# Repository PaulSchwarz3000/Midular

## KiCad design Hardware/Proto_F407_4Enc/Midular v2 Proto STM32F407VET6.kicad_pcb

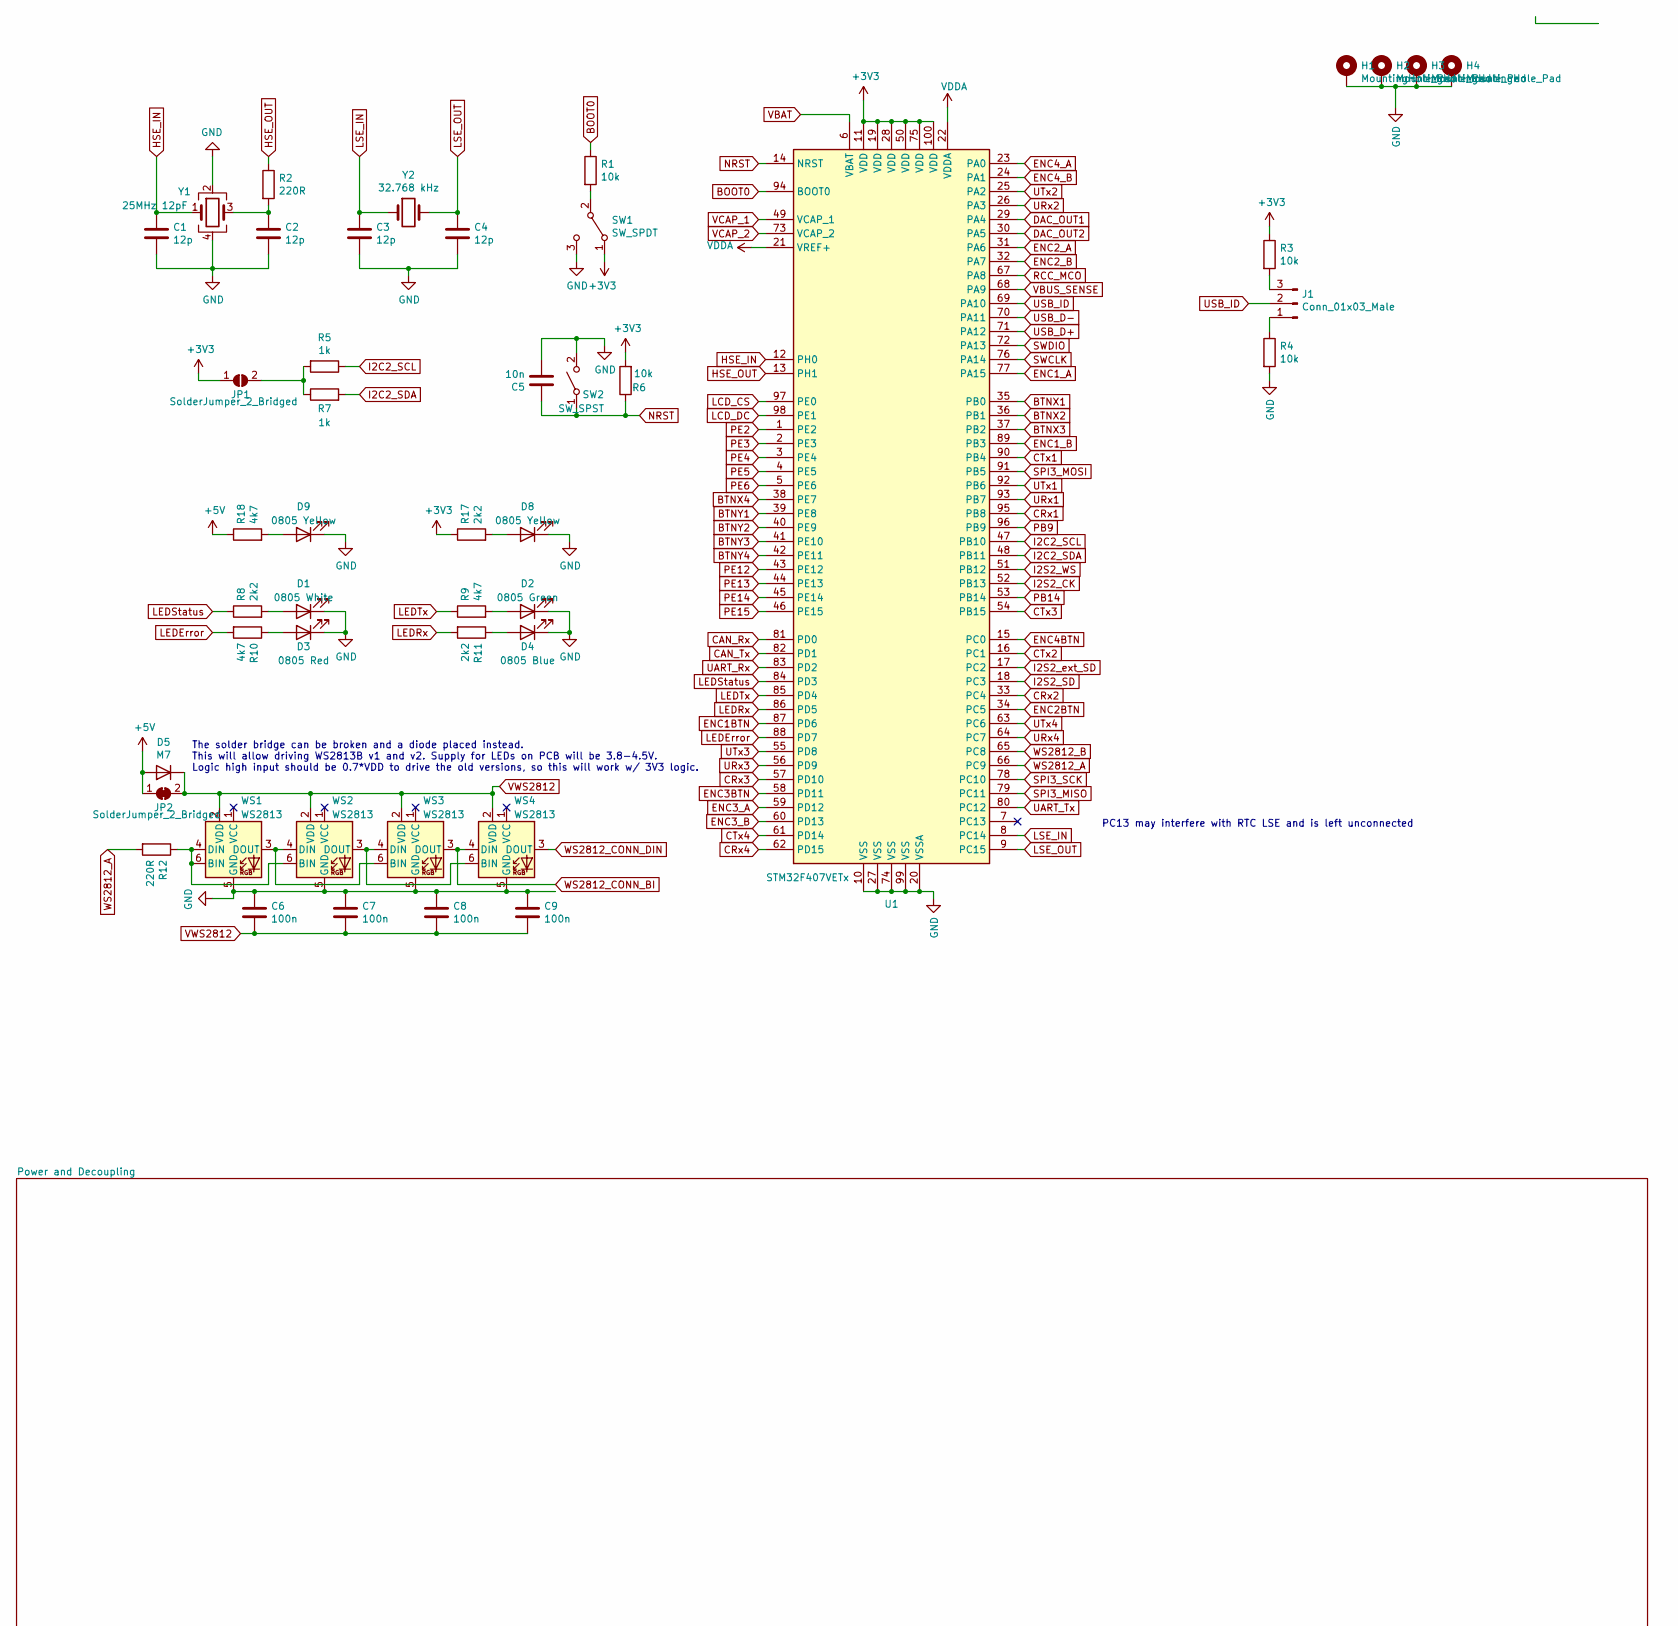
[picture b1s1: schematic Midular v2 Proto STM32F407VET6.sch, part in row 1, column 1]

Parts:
C1, C2, C3, C4: 12p; C_0603_1608Metric_Pad1.08x0.95mm_HandSolder; LCSC C38523
C5: 10n; C_0402_1005Metric_Pad0.74x0.62mm_HandSolder; LCSC C15195
C6, C7, C8, C9: 100n; C_0402_1005Metric; LCSC C1525
D1: 0805 White; LED_0805_2012Metric_Castellated; LCSC C34499
D2: 0805 Green; LED_0805_2012Metric_Castellated; LCSC C2297
D3: 0805 Red; LED_0805_2012Metric_Castellated; LCSC C84256
D4: 0805 Blue; LED_0805_2012Metric_Castellated; LCSC C2293
D5: M7; D_SMA; LCSC C95872
D8, D9: 0805 Yellow; LED_0805_2012Metric_Castellated; LCSC C2296
H1, H2, H3, H4: MountingHole_Pad; MountingHole_3.2mm_M3_ISO7380_Pad
J1: Conn_01x03_Male; PinHeader_1x03_P2.54mm_Vertical
JP1: SolderJumper_2_Bridged; SolderJumper-2_P1.3mm_Open_RoundedPad1.0x1.5mm
JP2: SolderJumper_2_Bridged; SolderJumper-2_P1.3mm_Bridged_RoundedPad1.0x1.5mm
R1, R3, R4, R6: 10k; R_0402_1005Metric; LCSC C25744
R2, R12: 220R; R_0805_2012Metric; LCSC C17557
R5, R7: 1k; R_1206_3216Metric_Pad1.30x1.75mm_HandSolder; LCSC C4410
R8, R11, R17: 2k2; R_0805_2012Metric_Pad1.20x1.40mm_HandSolder; LCSC C17520
R9, R10, R18: 4k7; R_0805_2012Metric_Pad1.20x1.40mm_HandSolder; LCSC C17673
SW1: SW_SPDT; SK3296S01L3; LCSC C319019
SW2: SW_SPST; K21107STA4SW06; LCSC C11814
U1: STM32F407VETx; LQFP-100_14x14mm_P0.5mm; LCSC C28730
WS1, WS2, WS3, WS4: WS2813; LED_WS2812_PLCC6_5.0x5.0mm_P1.6mm
Y1: 25MHz 12pF; Crystal_SMD_3225-4Pin_3.2x2.5mm; Part Nr X322525MOB4SI; LCSC C9006
Y2: 32.768 kHz; Crystal_SMD_3215-2Pin_3.2x1.5mm; LCSC C32346

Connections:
+3V3: JP1.1 (A), R3.1, R6.2, R17.1, SW1.1 (A), U1.11 (VDD), U1.19 (VDD), U1.28 (VDD), U1.50 (VDD), U1.75 (VDD), U1.100 (VDD); also elsewhere on the board
+5V: D5.2 (A), JP2.1 (A), R18.1; also elsewhere on the board
BOOT0: R1.1, U1.94 (BOOT0)
BTNX1: U1.35 (PB0); also elsewhere on the board
BTNX2: U1.36 (PB1); also elsewhere on the board
BTNX3: U1.37 (PB2); also elsewhere on the board
BTNX4: U1.38 (PE7); also elsewhere on the board
BTNY1: U1.39 (PE8); also elsewhere on the board
BTNY2: U1.40 (PE9); also elsewhere on the board
BTNY3: U1.41 (PE10); also elsewhere on the board
BTNY4: U1.42 (PE11); also elsewhere on the board
CAN_Rx: U1.81 (PD0); also elsewhere on the board
CAN_Tx: U1.82 (PD1); also elsewhere on the board
CRx1: U1.95 (PB8); also elsewhere on the board
CRx2: U1.33 (PC4); also elsewhere on the board
CRx3: U1.57 (PD10); also elsewhere on the board
CRx4: U1.62 (PD15); also elsewhere on the board
CTx1: U1.90 (PB4); also elsewhere on the board
CTx2: U1.16 (PC1); also elsewhere on the board
CTx3: U1.54 (PB15); also elsewhere on the board
CTx4: U1.61 (PD14); also elsewhere on the board
DAC_OUT1: U1.29 (PA4); also elsewhere on the board
DAC_OUT2: U1.30 (PA5); also elsewhere on the board
ENC1BTN: U1.87 (PD6); also elsewhere on the board
ENC1_A: U1.77 (PA15); also elsewhere on the board
ENC1_B: U1.89 (PB3); also elsewhere on the board
ENC2BTN: U1.34 (PC5); also elsewhere on the board
ENC2_A: U1.31 (PA6); also elsewhere on the board
ENC2_B: U1.32 (PA7); also elsewhere on the board
ENC3BTN: U1.58 (PD11); also elsewhere on the board
ENC3_A: U1.59 (PD12); also elsewhere on the board
ENC3_B: U1.60 (PD13); also elsewhere on the board
ENC4BTN: U1.15 (PC0); also elsewhere on the board
ENC4_A: U1.23 (PA0); also elsewhere on the board
ENC4_B: U1.24 (PA1); also elsewhere on the board
GND: C1.2, C2.2, C3.2, C4.2, C5.2, C6.1, C7.1, C8.1, C9.1, D1.1 (K), D2.1 (K), D3.1 (K), D4.1 (K), D8.1 (K), D9.1 (K), H1.1, H2.1, H3.1, H4.1, R4.2, SW1.3 (C), SW2.2 (B), U1.10 (VSS), U1.20 (VSSA), U1.27 (VSS), U1.74 (VSS), U1.99 (VSS), WS1.5 (GND), WS2.5 (GND), WS3.5 (GND), WS4.5 (GND), Y1.2, Y1.4; also elsewhere on the board
HSE_IN: C1.1, U1.12 (PH0), Y1.1
HSE_OUT: R2.1, U1.13 (PH1)
I2C2_SCL: R5.1, U1.47 (PB10); also elsewhere on the board
I2C2_SDA: R7.2, U1.48 (PB11); also elsewhere on the board
I2S2_CK: U1.52 (PB13); also elsewhere on the board
I2S2_SD: U1.18 (PC3); also elsewhere on the board
I2S2_WS: U1.51 (PB12); also elsewhere on the board
I2S2_ext_SD: U1.17 (PC2); also elsewhere on the board
LCD_CS: U1.97 (PE0); also elsewhere on the board
LCD_DC: U1.98 (PE1); also elsewhere on the board
LEDError: R10.2, U1.88 (PD7)
LEDRx: R11.2, U1.86 (PD5)
LEDStatus: R8.1, U1.84 (PD3)
LEDTx: R9.1, U1.85 (PD4)
LSE_IN: C3.1, U1.8 (PC14), Y2.1
LSE_OUT: C4.1, U1.9 (PC15), Y2.2
NRST: C5.1, R6.1, SW2.1 (A), U1.14 (NRST); also elsewhere on the board
unnamed: C2.1, R2.2, Y1.3
unnamed: D1.2 (A), R8.2
unnamed: D2.2 (A), R9.2
unnamed: D3.2 (A), R10.1
unnamed: D4.2 (A), R11.1
unnamed: D8.2 (A), R17.2
unnamed: D9.2 (A), R18.2
unnamed: J1.1, R4.1
unnamed: J1.3, R3.2
unnamed: JP1.2 (B), R5.2, R7.1
unnamed: R1.2, SW1.2 (B)
unnamed: R12.1, WS1.4 (DIN), WS1.6 (BIN), WS2.6 (BIN)
unnamed: WS1.3 (DOUT), WS2.4 (DIN), WS3.6 (BIN)
unnamed: WS2.3 (DOUT), WS3.4 (DIN), WS4.6 (BIN)
PB9: U1.96 (PB9); also elsewhere on the board
PB14: U1.53 (PB14); also elsewhere on the board
PE2: U1.1 (PE2); also elsewhere on the board
PE3: U1.2 (PE3); also elsewhere on the board
PE4: U1.3 (PE4); also elsewhere on the board
PE5: U1.4 (PE5); also elsewhere on the board
PE6: U1.5 (PE6); also elsewhere on the board
PE12: U1.43 (PE12); also elsewhere on the board
PE13: U1.44 (PE13); also elsewhere on the board
PE14: U1.45 (PE14); also elsewhere on the board
PE15: U1.46 (PE15); also elsewhere on the board
RCC_MCO: U1.67 (PA8); also elsewhere on the board
SPI3_MISO: U1.79 (PC11); also elsewhere on the board
SPI3_MOSI: U1.91 (PB5); also elsewhere on the board
SPI3_SCK: U1.78 (PC10); also elsewhere on the board
SWCLK: U1.76 (PA14); also elsewhere on the board
SWDIO: U1.72 (PA13); also elsewhere on the board
UART_Rx: U1.83 (PD2); also elsewhere on the board
UART_Tx: U1.80 (PC12); also elsewhere on the board
URx1: U1.93 (PB7); also elsewhere on the board
URx2: U1.26 (PA3); also elsewhere on the board
URx3: U1.56 (PD9); also elsewhere on the board
URx4: U1.64 (PC7); also elsewhere on the board
USB_D+: U1.71 (PA12); also elsewhere on the board
USB_D-: U1.70 (PA11); also elsewhere on the board
USB_ID: J1.2, U1.69 (PA10)
UTx1: U1.92 (PB6); also elsewhere on the board
UTx2: U1.25 (PA2); also elsewhere on the board
UTx3: U1.55 (PD8); also elsewhere on the board
UTx4: U1.63 (PC6); also elsewhere on the board
VBAT: U1.6 (VBAT); also elsewhere on the board
VBUS_SENSE: U1.68 (PA9); also elsewhere on the board
VCAP_1: U1.49 (VCAP_1); also elsewhere on the board
VCAP_2: U1.73 (VCAP_2); also elsewhere on the board
VDDA: U1.21 (VREF+), U1.22 (VDDA); also elsewhere on the board
VWS2812: C6.2, C7.2, C8.2, C9.2, D5.1 (K), JP2.2 (B), WS1.2 (VDD), WS2.2 (VDD), WS3.2 (VDD), WS4.2 (VDD)
WS2812_A: R12.2, U1.66 (PC9)
WS2812_B: U1.65 (PC8); also elsewhere on the board
WS2812_CONN_BI: WS3.3 (DOUT), WS4.4 (DIN); also elsewhere on the board
WS2812_CONN_DIN: WS4.3 (DOUT); also elsewhere on the board

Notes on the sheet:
The solder bridge can be broken and a diode placed instead. This will allow driving WS2813B v1 and v2. Supply for LEDs on PCB will be 3.8-4.5V. Logic high input should be 0.7*VDD to drive the old versions, so this will work w/ 3V3 logic.
PC13 may interfere with RTC LSE and is left unconnected

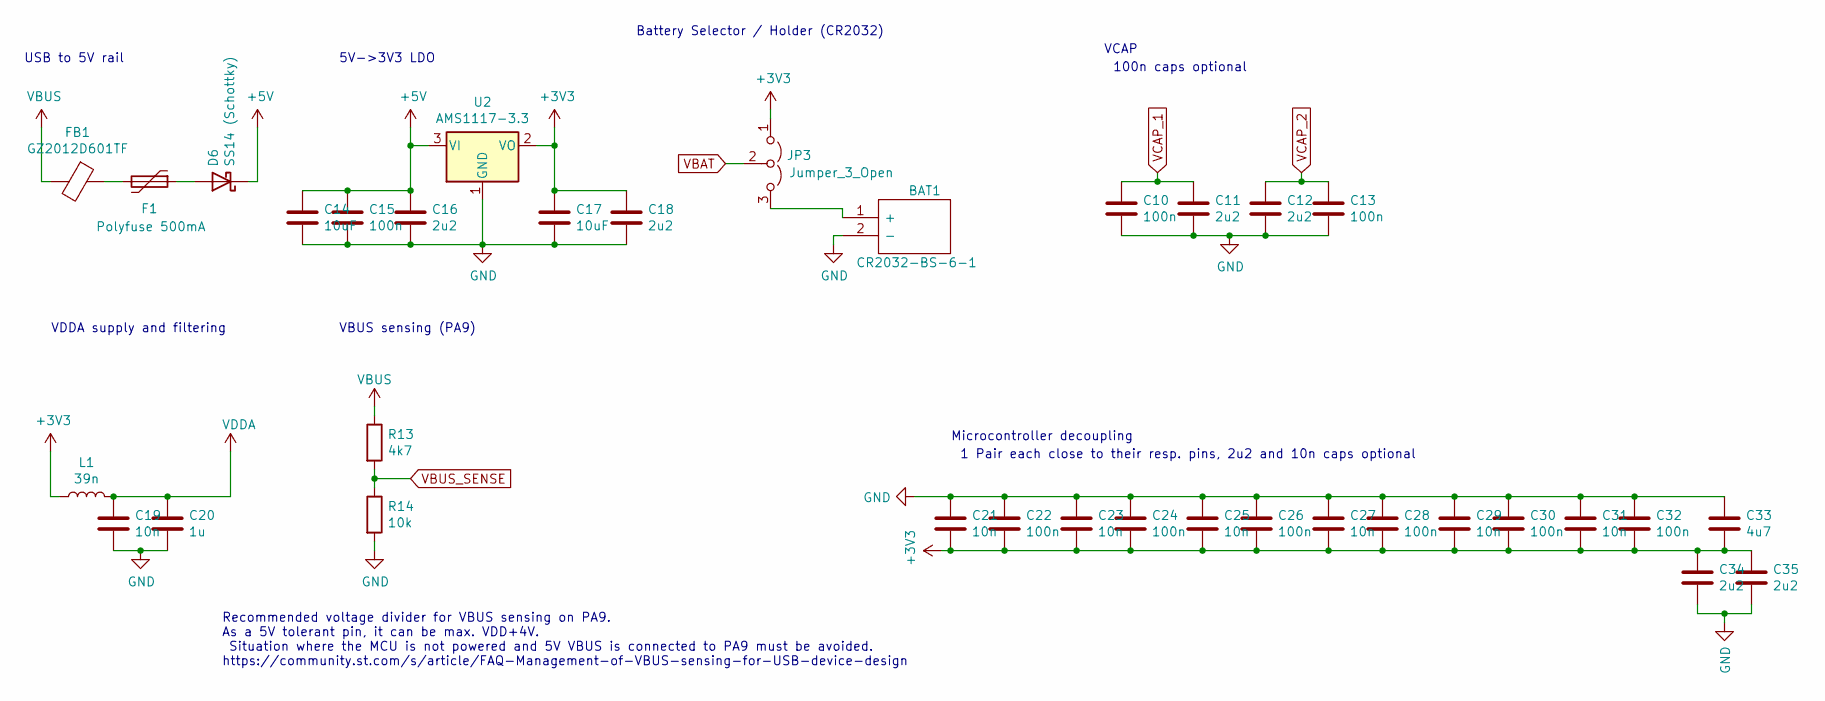
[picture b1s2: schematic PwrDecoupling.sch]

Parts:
BAT1: CR2032-BS-6-1; CR2032BS61; Manufacturer_Part_Number CR2032-BS-6-1
C10, C13, C15, C22, C24, C26, C28, C30, C32: 100n; C_0402_1005Metric; LCSC C1525
C11, C12, C16, C18, C34, C35: 2u2; C_0402_1005Metric; LCSC C12530
C14, C17: 10uF; C_0805_2012Metric_Pad1.18x1.45mm_HandSolder; LCSC C15850
C19, C21, C23, C25, C27, C29, C31: 10n; C_0402_1005Metric; LCSC C15195
C20: 1u; C_0402_1005Metric; LCSC C52923
C33: 4u7; C_0402_1005Metric; LCSC C19666
D6: SS14 (Schottky); D_SMA-SMB_Universal_Handsoldering; LCSC C2480
F1: Polyfuse 500mA; Fuse_1206_3216Metric_Castellated; LCSC C69688
FB1: GZ2012D601TF; L_0805_2012Metric; LCSC C1017
JP3: Jumper_3_Open; PinHeader_1x03_P2.54mm_Vertical
L1: 39n; L_0402_1005Metric; LCSC C26443
R13: 4k7; R_0402_1005Metric; LCSC C25900
R14: 10k; R_0402_1005Metric; LCSC C25744
U2: AMS1117-3.3; SOT-223-3_TabPin2; LCSC C6186

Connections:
+3V3: C17.1, C18.1, C21.2, C22.2, C23.2, C24.2, C25.2, C26.2, C27.2, C28.2, C29.2, C30.2, C31.2, C32.2, C33.2, C34.1, C35.1, JP3.1 (A), L1.1, U2.2 (VO); also elsewhere on the board
+5V: C14.1, C15.1, C16.1, D6.1 (K), U2.3 (VI); also elsewhere on the board
GND: BAT1.2 (-), C10.2, C11.2, C12.2, C13.2, C14.2, C15.2, C16.2, C17.2, C18.2, C19.2, C20.2, C21.1, C22.1, C23.1, C24.1, C25.1, C26.1, C27.1, C28.1, C29.1, C30.1, C31.1, C32.1, C33.1, C34.2, C35.2, R14.2, U2.1 (GND); also elsewhere on the board
unnamed: BAT1.1 (+), JP3.3 (B)
unnamed: D6.2 (A), F1.1
unnamed: F1.2, FB1.1
VBAT: JP3.2 (C); also elsewhere on the board
VBUS: FB1.2, R13.1; also elsewhere on the board
VBUS_SENSE: R13.2, R14.1; also elsewhere on the board
VCAP_1: C10.1, C11.1; also elsewhere on the board
VCAP_2: C12.1, C13.1; also elsewhere on the board
VDDA: C19.1, C20.1, L1.2; also elsewhere on the board

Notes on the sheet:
USB to 5V rail
Battery Selector / Holder (CR2032)
Microcontroller decoupling
1 Pair each close to their resp. pins, 2u2 and 10n caps optional
VCAP
100n caps optional
VDDA supply and filtering
VBUS sensing (PA9)
Recommended voltage divider for VBUS sensing on PA9. As a 5V tolerant pin, it can be max. VDD+4V. Situation where the MCU is not powered and 5V VBUS is connected to PA9 must be avoided. https://community.st.com/s/article/FAQ-Management-of-VBUS-sensing-for-USB-device-design
5V->3V3 LDO

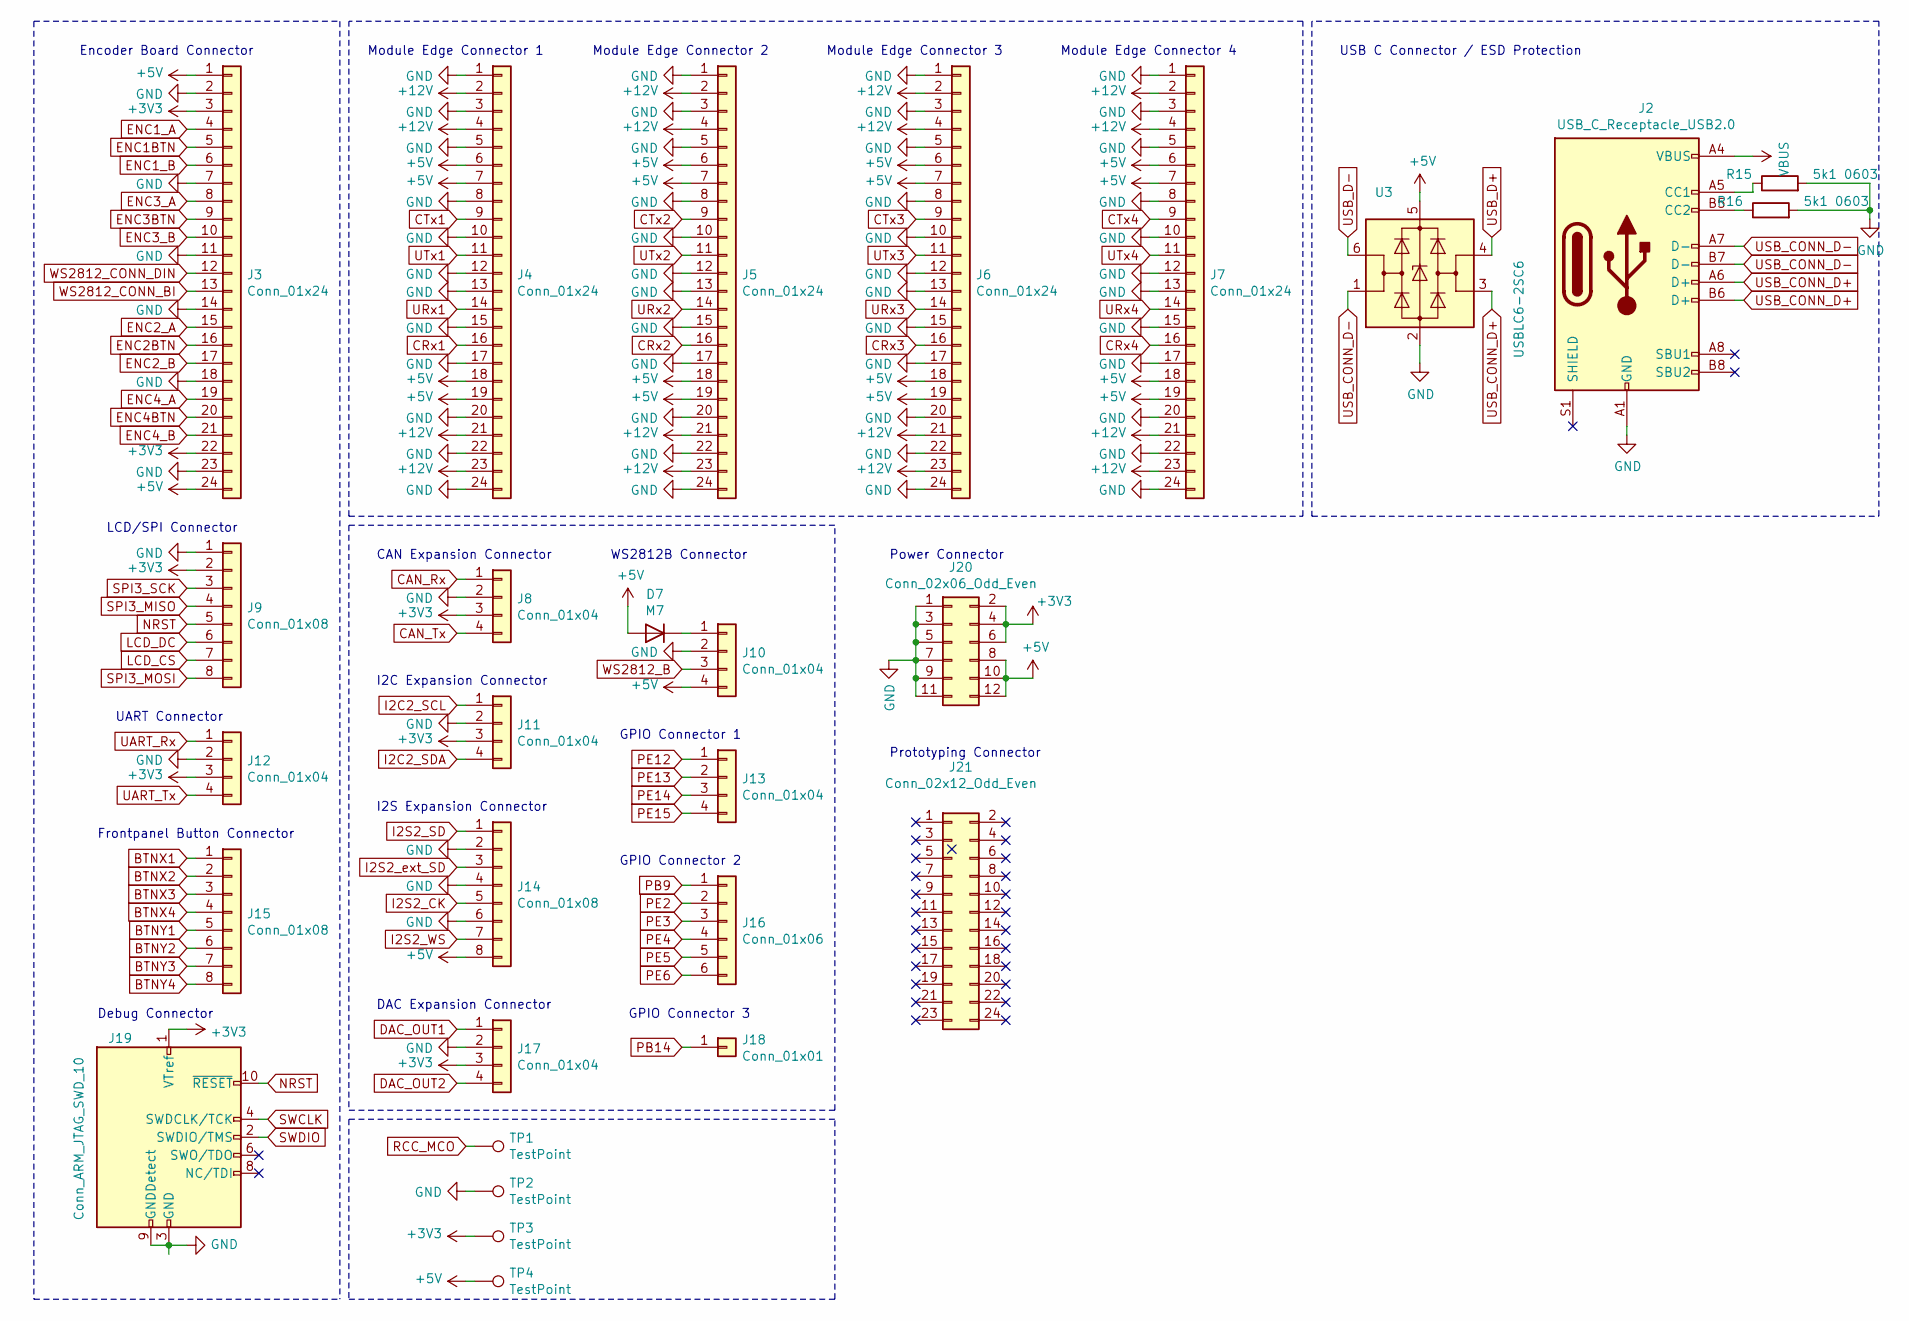
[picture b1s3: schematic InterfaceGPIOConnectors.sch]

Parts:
D7: M7; D_SMA; LCSC C95872
J2: USB_C_Receptacle_USB2.0; TYPEC304SACP16; LCSC C720630
J3: Conn_01x24; FPC_24_AFC24-S24FIC-00
J4, J5, J6, J7: Conn_01x24; FPC_24_AFC24-S24FIC-00; LCSC C262292
J8, J10, J11, J12, J13, J17: Conn_01x04; PinHeader_1x04_P2.54mm_Vertical
J9, J14, J15: Conn_01x08; PinHeader_1x08_P2.54mm_Vertical
J16: Conn_01x06; PinHeader_1x06_P2.54mm_Vertical
J18: Conn_01x01; PinHeader_1x01_P2.54mm_Vertical
J19: Conn_ARM_JTAG_SWD_10; PinHeader_2x05_P1.27mm_Vertical_SMD
J20: Conn_02x06_Odd_Even; PinHeader_2x06_P2.54mm_Vertical
J21: Conn_02x12_Odd_Even; PinHeader_2x12_P2.54mm_Vertical
R15, R16: 5k1 0603; R_0603_1608Metric_Pad0.98x0.95mm_HandSolder; LCSC C23186
TP1, TP2, TP3, TP4: TestPoint; TestPoint_Pad_D2.0mm
U3: USBLC6-2SC6; SOT-23-6; LCSC C7519

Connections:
+3V3: J3.3, J3.22, J8.3, J9.2, J11.3, J12.3, J17.3, J19.1 (VTref), J20.2, J20.4, J20.6, TP3.1; also elsewhere on the board
+5V: D7.2 (A), J3.1, J3.24, J4.6, J4.7, J4.18, J4.19, J5.6, J5.7, J5.18, J5.19, J6.6, J6.7, J6.18, J6.19, J7.6, J7.7, J7.18, J7.19, J10.4, J14.8, J20.8, J20.10, J20.12, TP4.1, U3.5 (VBUS); also elsewhere on the board
+12V: J4.2, J4.4, J4.21, J4.23, J5.2, J5.4, J5.21, J5.23, J6.2, J6.4, J6.21, J6.23, J7.2, J7.4, J7.21, J7.23
BTNX1: J15.1; also elsewhere on the board
BTNX2: J15.2; also elsewhere on the board
BTNX3: J15.3; also elsewhere on the board
BTNX4: J15.4; also elsewhere on the board
BTNY1: J15.5; also elsewhere on the board
BTNY2: J15.6; also elsewhere on the board
BTNY3: J15.7; also elsewhere on the board
BTNY4: J15.8; also elsewhere on the board
CAN_Rx: J8.1; also elsewhere on the board
CAN_Tx: J8.4; also elsewhere on the board
CRx1: J4.16; also elsewhere on the board
CRx2: J5.16; also elsewhere on the board
CRx3: J6.16; also elsewhere on the board
CRx4: J7.16; also elsewhere on the board
CTx1: J4.9; also elsewhere on the board
CTx2: J5.9; also elsewhere on the board
CTx3: J6.9; also elsewhere on the board
CTx4: J7.9; also elsewhere on the board
DAC_OUT1: J17.1; also elsewhere on the board
DAC_OUT2: J17.4; also elsewhere on the board
ENC1BTN: J3.5; also elsewhere on the board
ENC1_A: J3.4; also elsewhere on the board
ENC1_B: J3.6; also elsewhere on the board
ENC2BTN: J3.16; also elsewhere on the board
ENC2_A: J3.15; also elsewhere on the board
ENC2_B: J3.17; also elsewhere on the board
ENC3BTN: J3.9; also elsewhere on the board
ENC3_A: J3.8; also elsewhere on the board
ENC3_B: J3.10; also elsewhere on the board
ENC4BTN: J3.20; also elsewhere on the board
ENC4_A: J3.19; also elsewhere on the board
ENC4_B: J3.21; also elsewhere on the board
GND: J2.A1 (GND), J2.A12 (GND), J2.B1 (GND), J2.B12 (GND), J3.2, J3.7, J3.11, J3.14, J3.18, J3.23, J4.1, J4.3, J4.5, J4.8, J4.10, J4.12, J4.13, J4.15, J4.17, J4.20, J4.22, J4.24, J5.1, J5.3, J5.5, J5.8, J5.10, J5.12, J5.13, J5.15, J5.17, J5.20, J5.22, J5.24, J6.1, J6.3, J6.5, J6.8, J6.10, J6.12, J6.13, J6.15, J6.17, J6.20, J6.22, J6.24, J7.1, J7.3, J7.5, J7.8, J7.10, J7.12, J7.13, J7.15, J7.17, J7.20, J7.22, J7.24, J8.2, J9.1, J10.2, J11.2, J12.2, J14.2, J14.4, J14.6, J17.2, J19.3 (GND), J19.5 (GND), J19.9 (GNDDetect), J20.1, J20.3, J20.5, J20.7, J20.9, J20.11, R15.2, R16.2, TP2.1, U3.2 (GND); also elsewhere on the board
I2C2_SCL: J11.1; also elsewhere on the board
I2C2_SDA: J11.4; also elsewhere on the board
I2S2_CK: J14.5; also elsewhere on the board
I2S2_SD: J14.1; also elsewhere on the board
I2S2_WS: J14.7; also elsewhere on the board
I2S2_ext_SD: J14.3; also elsewhere on the board
LCD_CS: J9.7; also elsewhere on the board
LCD_DC: J9.6; also elsewhere on the board
NRST: J9.5, J19.10 (~RESET~); also elsewhere on the board
unnamed: D7.1 (K), J10.1
unnamed: J2.A5 (CC1), R15.1
unnamed: J2.B5 (CC2), R16.1
PB9: J16.1; also elsewhere on the board
PB14: J18.1; also elsewhere on the board
PE2: J16.2; also elsewhere on the board
PE3: J16.3; also elsewhere on the board
PE4: J16.4; also elsewhere on the board
PE5: J16.5; also elsewhere on the board
PE6: J16.6; also elsewhere on the board
PE12: J13.1; also elsewhere on the board
PE13: J13.2; also elsewhere on the board
PE14: J13.3; also elsewhere on the board
PE15: J13.4; also elsewhere on the board
RCC_MCO: TP1.1; also elsewhere on the board
SPI3_MISO: J9.4; also elsewhere on the board
SPI3_MOSI: J9.8; also elsewhere on the board
SPI3_SCK: J9.3; also elsewhere on the board
SWCLK: J19.4 (SWDCLK/TCK); also elsewhere on the board
SWDIO: J19.2 (SWDIO/TMS); also elsewhere on the board
UART_Rx: J12.1; also elsewhere on the board
UART_Tx: J12.4; also elsewhere on the board
URx1: J4.14; also elsewhere on the board
URx2: J5.14; also elsewhere on the board
URx3: J6.14; also elsewhere on the board
URx4: J7.14; also elsewhere on the board
USB_CONN_D+: J2.A6 (D+), J2.B6 (D+), U3.3 (I/O2)
USB_CONN_D-: J2.A7 (D-), J2.B7 (D-), U3.1 (I/O1)
USB_D+: U3.4 (I/O2); also elsewhere on the board
USB_D-: U3.6 (I/O1); also elsewhere on the board
UTx1: J4.11; also elsewhere on the board
UTx2: J5.11; also elsewhere on the board
UTx3: J6.11; also elsewhere on the board
UTx4: J7.11; also elsewhere on the board
VBUS: J2.A4 (VBUS), J2.A9 (VBUS), J2.B4 (VBUS), J2.B9 (VBUS); also elsewhere on the board
WS2812_B: J10.3; also elsewhere on the board
WS2812_CONN_BI: J3.13; also elsewhere on the board
WS2812_CONN_DIN: J3.12; also elsewhere on the board

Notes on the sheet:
Encoder Board Connector
Module Edge Connector 1
I2S Expansion Connector
CAN Expansion Connector
I2C Expansion Connector
LCD/SPI Connector
DAC Expansion Connector
UART Connector
Module Edge Connector 2
Module Edge Connector 3
Module Edge Connector 4
Debug Connector
WS2812B Connector
USB C Connector / ESD Protection
Frontpanel Button Connector
GPIO Connector 1
GPIO Connector 2
GPIO Connector 3
Power Connector
Prototyping Connector

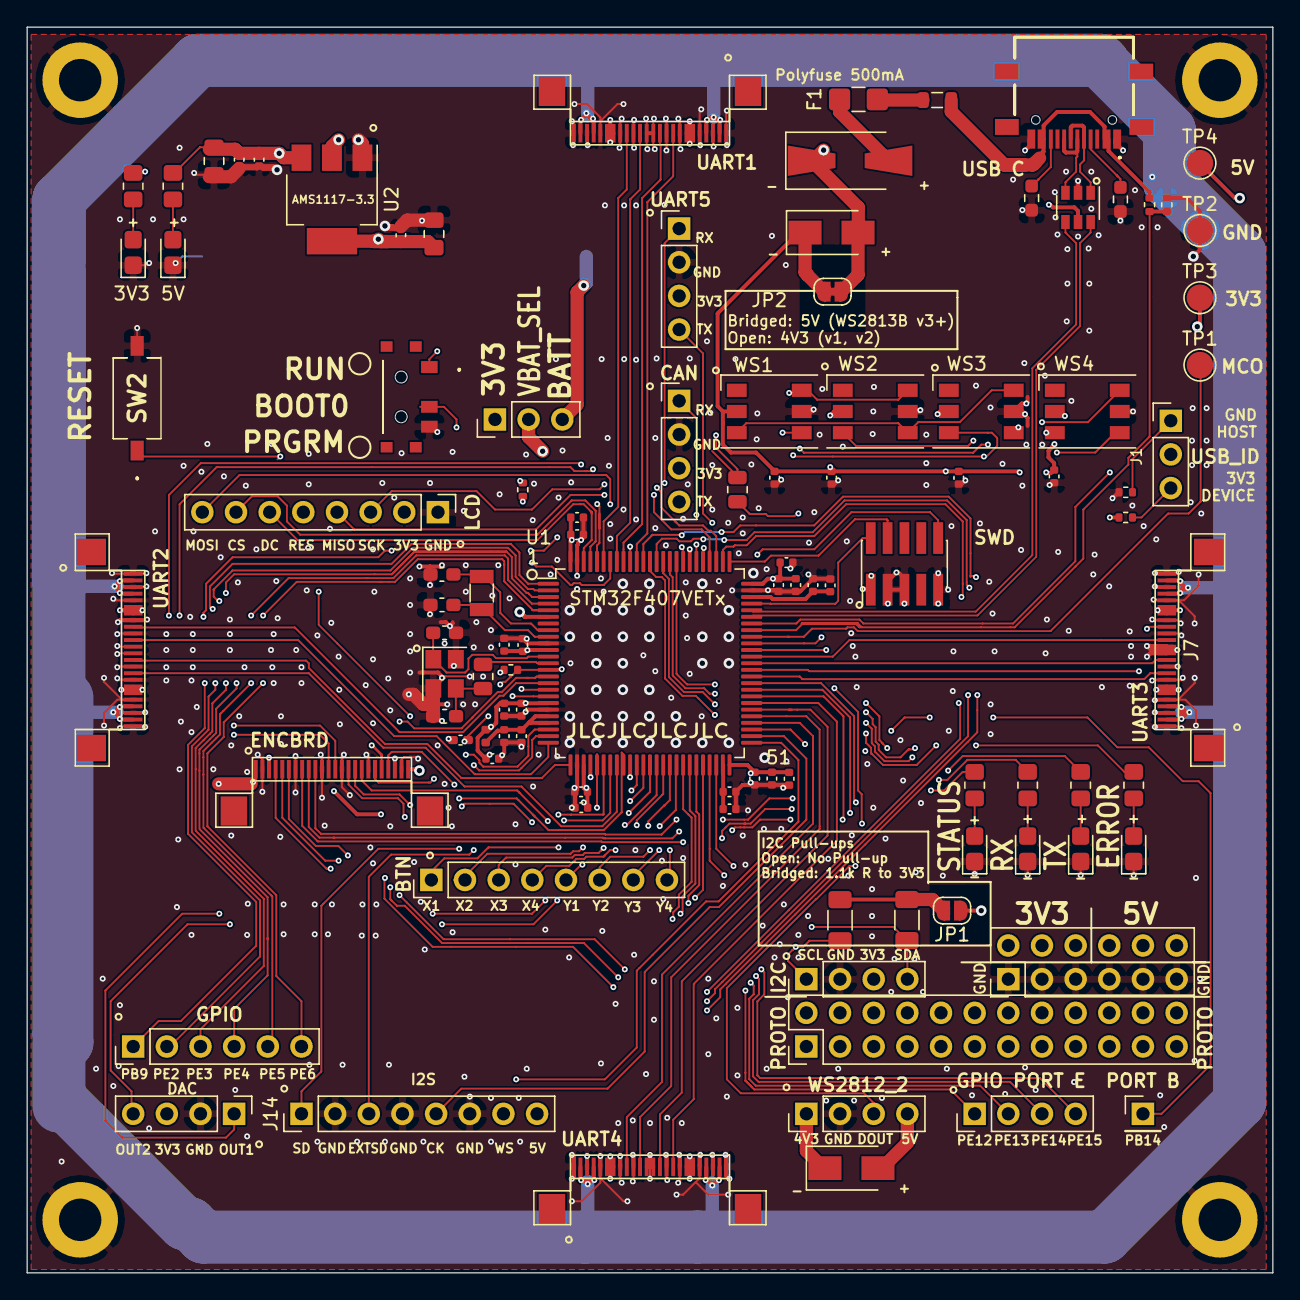
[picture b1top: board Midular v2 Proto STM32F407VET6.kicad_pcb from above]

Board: 4 copper layers, 94.0 x 94.0 mm, 109 parts (1 on the bottom side), 117 nets.

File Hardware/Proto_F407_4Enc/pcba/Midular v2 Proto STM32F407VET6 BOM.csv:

Comment,Designator,Footprint,LCSC
"CR2032-BS-6-1","BAT1","CR2032:CR2032BS61",""
"12p","C1,C2,C3,C4","Capacitor_SMD:C_0603_1608Metric_Pad1.08x0.95mm_HandSolder","C38523"
"2u2","C11,C12,C16,C18,C34,C35","Capacitor_SMD:C_0402_1005Metric","C12530"
"10uF","C14,C17","Capacitor_SMD:C_0805_2012Metric_Pad1.18x1.45mm_HandSolder","C15850"
"1u","C20","Capacitor_SMD:C_0402_1005Metric","C52923"
"10n","C19,C21,C23,C25,C27,C29,C31","Capacitor_SMD:C_0402_1005Metric","C15195"
"4u7","C33","Capacitor_SMD:C_0402_1005Metric","C19666"
"10n","C5","Capacitor_SMD:C_0402_1005Metric_Pad0.74x0.62mm_HandSolder","C15195"
"100n","C6,C7,C8,C9,C10,C13,C15,C22,C24,C26,C28,C30,C32","Capacitor_SMD:C_0402_1005Metric","C1525"
"0805 White","D1","LED_SMD:LED_0805_2012Metric_Castellated","C34499"
"0805 Green","D2","LED_SMD:LED_0805_2012Metric_Castellated","C2297"
"0805 Red","D3","LED_SMD:LED_0805_2012Metric_Castellated","C84256"
"0805 Blue","D4","LED_SMD:LED_0805_2012Metric_Castellated","C2293"
"M7","D5,D7","Diode_SMD:D_SMA","C95872"
"SS14 (Schottky)","D6","Diode_SMD:D_SMA-SMB_Universal_Handsoldering","C2480"
"0805 Yellow","D8,D9","LED_SMD:LED_0805_2012Metric_Castellated"," C2296"
"Polyfuse 500mA","F1","Fuse:Fuse_1206_3216Metric_Castellated","C69688"
"GZ2012D601TF","FB1","Inductor_SMD:L_0805_2012Metric","C1017"
"MountingHole_Pad","H1,H2,H3,H4","MountingHole:MountingHole_3.2mm_M3_ISO7380_Pad",""
"Conn_01x03_Male","J1","Connector_PinHeader_2.54mm:PinHeader_1x03_P2.54mm_Vertical",""
"Conn_01x08","J9,J14,J15","Connector_PinHeader_2.54mm:PinHeader_1x08_P2.54mm_Vertical",""
"Conn_01x06","J16","Connector_PinHeader_2.54mm:PinHeader_1x06_P2.54mm_Vertical",""
"Conn_01x01","J18","Connector_PinHeader_2.54mm:PinHeader_1x01_P2.54mm_Vertical",""
"Conn_ARM_JTAG_SWD_10","J19","Connector_PinHeader_1.27mm:PinHeader_2x05_P1.27mm_Vertical_SMD",""
"USB_C_Receptacle_USB2.0","J2","Connectors_USBC_TYPEC-304S-ACP16:TYPEC304SACP16"," C720630"
"Conn_02x06_Odd_Even","J20","Connector_PinHeader_2.54mm:PinHeader_2x06_P2.54mm_Vertical",""
"Conn_02x12_Odd_Even","J21","Connector_PinHeader_2.54mm:PinHeader_2x12_P2.54mm_Vertical",""
"Conn_01x24","J3,J4,J5,J6,J7","PaulSchwarz_ConnFPC_1x24_AFC24-S24FIC-00:FPC_24_AFC24-S24FIC-00","C262292"
"Conn_01x04","J8,J10,J11,J12,J13,J17","Connector_PinHeader_2.54mm:PinHeader_1x04_P2.54mm_Vertical",""
"SolderJumper_2_Bridged","JP1","Jumper:SolderJumper-2_P1.3mm_Open_RoundedPad1.0x1.5mm",""
"SolderJumper_2_Bridged","JP2","Jumper:SolderJumper-2_P1.3mm_Bridged_RoundedPad1.0x1.5mm",""
"Jumper_3_Open","JP3","Connector_PinHeader_2.54mm:PinHeader_1x03_P2.54mm_Vertical",""
"39n","L1","Inductor_SMD:L_0402_1005Metric","C26443"
"10k","R1,R3,R4,R6,R14","Resistor_SMD:R_0402_1005Metric"," C25744"
"4k7","R9,R10,R18","Resistor_SMD:R_0805_2012Metric_Pad1.20x1.40mm_HandSolder","C17673"
"4k7","R13","Resistor_SMD:R_0402_1005Metric","C25900"
"5k1 0603","R15,R16","Resistor_SMD:R_0603_1608Metric_Pad0.98x0.95mm_HandSolder","C23186"
"220R","R2,R12","Resistor_SMD:R_0805_2012Metric"," C17557"
"1k","R5,R7","Resistor_SMD:R_1206_3216Metric_Pad1.30x1.75mm_HandSolder","C4410"
"2k2","R8,R11,R17","Resistor_SMD:R_0805_2012Metric_Pad1.20x1.40mm_HandSolder","C17520"
"SW_SPDT","SW1","Switches_DPDT_SK-3296S-01-L3:SK3296S01L3","C319019"
"SW_SPST","SW2","Switches_SPST_3.6x6.1mm_K2-1107ST-A4SW-06:K21107STA4SW06","C11814"
"TestPoint","TP1,TP2,TP3,TP4","TestPoint:TestPoint_Pad_D2.0mm",""
"STM32F407VETx","U1","Package_QFP:LQFP-100_14x14mm_P0.5mm","C28730"
"AMS1117-3.3","U2","Package_TO_SOT_SMD:SOT-223-3_TabPin2","C6186"
"USBLC6-2SC6","U3","Package_TO_SOT_SMD:SOT-23-6","C7519"
"WS2813","WS1,WS2,WS3,WS4","LED_SMD:LED_WS2812_PLCC6_5.0x5.0mm_P1.6mm",""
"25MHz 12pF","Y1","Crystal:Crystal_SMD_3225-4Pin_3.2x2.5mm","C9006"
"32.768 kHz","Y2","Crystal:Crystal_SMD_3215-2Pin_3.2x1.5mm","C32346"
